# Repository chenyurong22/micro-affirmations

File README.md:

# µAffirmations
A microcontroller-based affection-giving MACHINE!

> [!IMPORTANT]
> This project is currently a work-in-progress, there __will__ be things that don't work, please bear with me will I work out the kinks!

# Table of Contents
- [Usage Guide](#usage-guide)
  - [Hardware](#hardware)
  - [Firmware](#firmware)
- [Project Updates](#project-updates)
- [Copyright and Licensing](#copyright-and-licensing)
- [Contact](#contact)

# Usage Guide
## Hardware
The PCB files can be found [here](/hw/pcb/RevB.zip), be sure of order a solder stencil too(ideally with a stencil unless you love hand-soldering 200+ SMD connections). The [BOM](/hw/pcb/micro-affirmations_BOM.csv) will provide you with a list of parts required. Due to the limited size on the PCB, many of the reference designators have been removed to save space. Because of this, you will likely need to have KiCAD running as you are placing components.

## Firmware
You will need access to an ST-Link programming device and have Platform IO installed via VS code. Once you're ready, upload the code by:
- Cloning the repository
- Open in VS code
- Connect the ST-Link programmer to your computer
- Connect the µAffirmations' programming port to the ST-Link programmer
- Ensure the µAffirmations board is powered
- Open the STM32 for VS Code extention
- Click __Upload__

<!--
### Message customisation
This device allows the user to create their own custom messages to be displayed on the LED matrix, to provide your messages, modify the following code found in [this](/path/to/file.c) file.

For axample:
```c
uint8_t someVar = 0;
```
-->

# Project Updates
## Hardware [RevB](https://github.com/i-Saac-IV/micro-affirmations/tree/v0.9.1)
After hardware tesing the following fixes have been made to the hardware design:
- Supercapcitor charging circuit, now uses a dedecated IC
- LED matrix layout, the LED spacing has been decreased
- LED brightness was assessed and appropriate resistor have been selected
- The overall PCB dimentions have shrunk to 70x40mm

## Hardware [RevA](https://github.com/i-Saac-IV/micro-affirmations/tree/v0.9.0)
Initial hardware design.

# Copyright and Licensing
See [licence](LICENSE) for in depth info.
<!--
This project uses the following third-party libraries:

- Lib ( License)

Copyright and license terms belong to their respective authors.

Contact me if anything here is incorrect.
-->

# Contact
If you'd like to get in touch, feel free to reach out!
<p>

</p>

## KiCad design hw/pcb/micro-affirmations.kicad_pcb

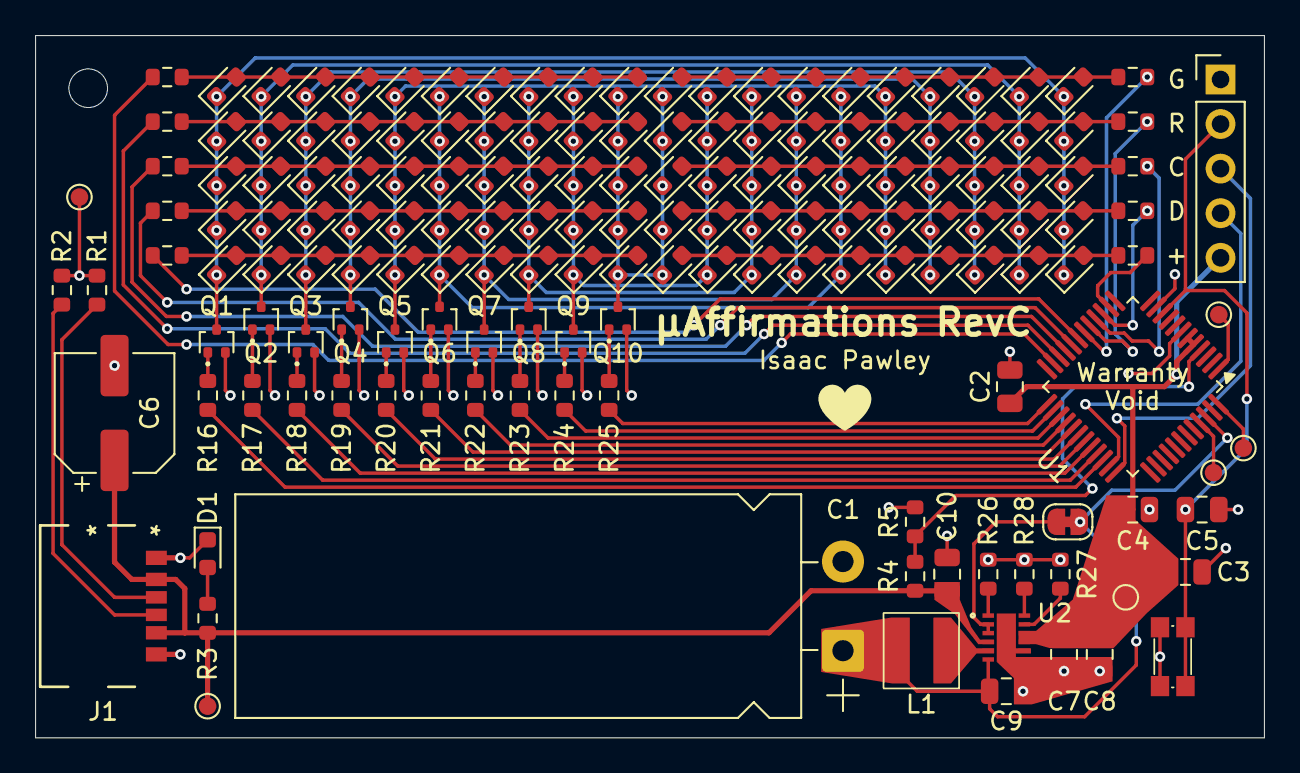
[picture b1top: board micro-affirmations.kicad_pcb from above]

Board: 2 copper layers, 70.0 x 40.0 mm, 164 parts (1 on the bottom side), 70 nets.

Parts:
C1: 15F; CP_Radial_L32.0mm_D12.5mm_P5.00mm_Horizontal
C2: 4.7u; C_0805_2012Metric
C3, C4, C5: 100n; C_0805_2012Metric
C6: 100u; CP_Elec_6.3x5.4_Nichicon
C7, C8, C9, C10: 10u; C_0805_2012Metric
D1: CHARGE; D_0603_1608Metric
D5, D6, D7, D8, D9, D10, D11, D12, D13, D14, D15, D16, D17, D18, D19, D20, D21, D22, D23, D24, D25, D26, D27, D28, D29, D30, D31, D32, D33, D34, D35, D36, D37, D38, D39, D40, D41, D42, D43, D44, D45, D46, D47, D48, D49, D50, D51, D52, D53, D54, D55, D56, D57, D58, D59, D60, D61, D62, D63, D64, D65, D66, D67, D68, D69, D70, D71, D72, D73, D74, D75, D76, D77, D78, D79, D80, D81, D82, D83, D84, D85, D86, D87, D88, D89, D90, D91, D92, D93, D94, D95, D96, D97, D98, D99, D100, D101, D102, D103, D104: LED; D_0603_1608Metric
H1: MountingHole; MountingHole_2.2mm_M2
J1: USBC; 2171750001_MOL
J2: DEBUG; PinHeader_1x05_P2.54mm_Vertical
JP1: SolderJumper_2_Bridged; SolderJumper-2_P1.3mm_Bridged_RoundedPad1.0x1.5mm
L1: 2.2u; L_1616_4040Metric
Q1, Q2, Q3, Q4, Q5, Q6, Q7, Q8, Q9, Q10: NCH; SOT-416
R1, R2, R4: 5.1k; R_0603_1608Metric
R3: 1.5k; R_0603_1608Metric
R5: 10k; R_0603_1608Metric
R6, R7, R8, R9, R10, R11, R12, R13, R14, R15: 820; R_0603_1608Metric
R16, R17, R18, R19, R20, R21, R22, R23, R24, R25: 100; R_0603_1608Metric
R26: 4.75k; R_0603_1608Metric
R27: 75.0k; R_0603_1608Metric
R28: 13.0k; R_0603_1608Metric
SW1: RST; TL1030_A
TP2, TP3, TP4, TP5, TP6, TP7, TP8: TestPoint; TestPoint_Pad_D1.0mm
U1: STM32C031C6Tx; LQFP-48_7x7mm_P0.5mm
U2: TPS61094; WSON_94DSSR_TEX

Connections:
+3V3: C2.1, C3.1, C4.1, C7.1, C8.1, J2.5, TP3.1 (1_1), U1.5 (VREF+), U1.6 (VDD), U2.9 (VOUT), U2.10 (VOUT)
+5V: C6.1, C10.1, J1.A9 (VBUS), J1.B9 (VBUS), R3.1, R4.2, TP2.1 (1_1), U2.4 (VIN)
/CHARGE_SENSE: R4.1, R5.2, U1.4 (PF3)
/DEBUG_SWCLK: J2.3, U1.36 (PA14)
/DEBUG_SWDIO: J2.4, U1.35 (PA13)
/MATRIX_A0: R6.1, U1.23 (PB11)
/MATRIX_A1: R7.1, U1.22 (PB10)
/MATRIX_A2: R8.1, U1.21 (PB2)
/MATRIX_A3: R9.1, U1.20 (PB1)
/MATRIX_A4: R10.1, U1.19 (PB0)
/MATRIX_A5: R11.1, U1.18 (PA7)
/MATRIX_A6: R12.1, U1.17 (PA6)
/MATRIX_A7: R13.1, U1.16 (PA5)
/MATRIX_A8: R14.1, U1.15 (PA4)
/MATRIX_A9: R15.1, U1.14 (PA3)
/MATRIX_K0: R16.1, U1.34 (PA12)
/MATRIX_K1: R17.1, U1.33 (PA11)
/MATRIX_K2: R18.1, U1.32 (PA10)
/MATRIX_K3: R19.1, U1.31 (PC7)
/MATRIX_K4: R20.1, U1.30 (PC6)
/MATRIX_K5: R21.1, U1.29 (PA9)
/MATRIX_K6: R22.1, U1.28 (PA8)
/MATRIX_K7: R23.1, U1.27 (PB15)
/MATRIX_K8: R24.1, U1.26 (PB14)
/MATRIX_K9: R25.1, U1.25 (PB13)
/NRST: C5.1, J2.2, SW1.2, U1.10 (PF2)
CAP_VOLT: C1.1, C9.1, JP1.1 (A), L1.2, U1.46 (PB7), U2.6 (SUP)
GND: C1.2, C2.2, C3.2, C4.2, C5.2, C6.2, C7.2, C8.2, C9.2, C10.2, D1.1 (K), J1.A12 (GND), J1.B12 (GND), J2.1, Q1.2 (S), Q2.2 (S), Q3.2 (S), Q4.2 (S), Q5.2 (S), Q6.2 (S), Q7.2 (S), Q8.2 (S), Q9.2 (S), Q10.2 (S), R1.2, R2.2, R5.1, R26.1, R27.1, R28.1, SW1.1, TP8.1 (1_1), U1.7 (VSS), U2.7 (PGND), U2.8 (AGND), U2.13
unnamed: D1.2 (A), R3.2
unnamed: D5.2 (A), D6.2 (A), D7.2 (A), D8.2 (A), D9.2 (A), D10.2 (A), D11.2 (A), D12.2 (A), D13.2 (A), D14.2 (A), R6.2
unnamed: D10.1 (K), D20.1 (K), D30.1 (K), D40.1 (K), D50.1 (K), D60.1 (K), D70.1 (K), D80.1 (K), D90.1 (K), D100.1 (K), Q6.3 (D)
unnamed: D15.2 (A), D16.2 (A), D17.2 (A), D18.2 (A), D19.2 (A), D20.2 (A), D21.2 (A), D22.2 (A), D23.2 (A), D24.2 (A), R7.2
unnamed: D5.1 (K), D15.1 (K), D25.1 (K), D35.1 (K), D45.1 (K), D55.1 (K), D65.1 (K), D75.1 (K), D85.1 (K), D95.1 (K), Q1.3 (D)
unnamed: D6.1 (K), D16.1 (K), D26.1 (K), D36.1 (K), D46.1 (K), D56.1 (K), D66.1 (K), D76.1 (K), D86.1 (K), D96.1 (K), Q2.3 (D)
unnamed: D7.1 (K), D17.1 (K), D27.1 (K), D37.1 (K), D47.1 (K), D57.1 (K), D67.1 (K), D77.1 (K), D87.1 (K), D97.1 (K), Q3.3 (D)
unnamed: D8.1 (K), D18.1 (K), D28.1 (K), D38.1 (K), D48.1 (K), D58.1 (K), D68.1 (K), D78.1 (K), D88.1 (K), D98.1 (K), Q4.3 (D)
unnamed: D9.1 (K), D19.1 (K), D29.1 (K), D39.1 (K), D49.1 (K), D59.1 (K), D69.1 (K), D79.1 (K), D89.1 (K), D99.1 (K), Q5.3 (D)
unnamed: D25.2 (A), D26.2 (A), D27.2 (A), D28.2 (A), D29.2 (A), D30.2 (A), D31.2 (A), D32.2 (A), D33.2 (A), D34.2 (A), R8.2
unnamed: D35.2 (A), D36.2 (A), D37.2 (A), D38.2 (A), D39.2 (A), D40.2 (A), D41.2 (A), D42.2 (A), D43.2 (A), D44.2 (A), R9.2
unnamed: D45.2 (A), D46.2 (A), D47.2 (A), D48.2 (A), D49.2 (A), D50.2 (A), D51.2 (A), D52.2 (A), D53.2 (A), D54.2 (A), R10.2
unnamed: D55.2 (A), D56.2 (A), D57.2 (A), D58.2 (A), D59.2 (A), D60.2 (A), D61.2 (A), D62.2 (A), D63.2 (A), D64.2 (A), R11.2
unnamed: D65.2 (A), D66.2 (A), D67.2 (A), D68.2 (A), D69.2 (A), D70.2 (A), D71.2 (A), D72.2 (A), D73.2 (A), D74.2 (A), R12.2
unnamed: D75.2 (A), D76.2 (A), D77.2 (A), D78.2 (A), D79.2 (A), D80.2 (A), D81.2 (A), D82.2 (A), D83.2 (A), D84.2 (A), R13.2
unnamed: D85.2 (A), D86.2 (A), D87.2 (A), D88.2 (A), D89.2 (A), D90.2 (A), D91.2 (A), D92.2 (A), D93.2 (A), D94.2 (A), R14.2
unnamed: D95.2 (A), D96.2 (A), D97.2 (A), D98.2 (A), D99.2 (A), D100.2 (A), D101.2 (A), D102.2 (A), D103.2 (A), D104.2 (A), R15.2
unnamed: D11.1 (K), D21.1 (K), D31.1 (K), D41.1 (K), D51.1 (K), D61.1 (K), D71.1 (K), D81.1 (K), D91.1 (K), D101.1 (K), Q7.3 (D)
unnamed: D12.1 (K), D22.1 (K), D32.1 (K), D42.1 (K), D52.1 (K), D62.1 (K), D72.1 (K), D82.1 (K), D92.1 (K), D102.1 (K), Q8.3 (D)
unnamed: D13.1 (K), D23.1 (K), D33.1 (K), D43.1 (K), D53.1 (K), D63.1 (K), D73.1 (K), D83.1 (K), D93.1 (K), D103.1 (K), Q9.3 (D)
unnamed: D14.1 (K), D24.1 (K), D34.1 (K), D44.1 (K), D54.1 (K), D64.1 (K), D74.1 (K), D84.1 (K), D94.1 (K), D104.1 (K), Q10.3 (D)
unnamed: J1.A5 (CC1), R1.1
unnamed: J1.B5 (CC2), R2.1
unnamed: JP1.2 (B), U2.2 (MODE), U2.3 (EN)
unnamed: Q1.1 (G), R16.2
unnamed: Q2.1 (G), R17.2
unnamed: Q3.1 (G), R18.2
unnamed: Q4.1 (G), R19.2
unnamed: Q5.1 (G), R20.2
unnamed: Q6.1 (G), R21.2
unnamed: Q7.1 (G), R22.2
unnamed: Q8.1 (G), R23.2
unnamed: Q9.1 (G), R24.2
unnamed: Q10.1 (G), R25.2
unnamed: TP7.1 (1_1), U1.11 (PA0)
unnamed: TP5.1 (1_1), U1.45 (PB6)
unnamed: TP4.1 (1_1), U1.48 (PB9)
unnamed: TP6.1 (1_1), U1.1 (PC13)
unnamed: R27.2, U2.11 (ICHG)
unnamed: R26.2, U2.1 (OSEL)
unnamed: L1.1, U2.5 (SW)
unnamed: R28.2, U2.12 (VCHG)

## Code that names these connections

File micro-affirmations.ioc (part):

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Mcu.Name=STM32C031C(4-6)Tx
Mcu.Package=LQFP48
Mcu.UserName=STM32C031C6Tx
PA1.GPIOParameters=GPIO_Label
PA1.GPIO_Label=RANDOM
PA1.Mode=IN1
PA1.Signal=ADC1_IN1
PA10.GPIOParameters=GPIO_Label
PA10.GPIO_Label=MATRIX_K2
PA10.Signal=GPIO_Output
PA11\ [PA9].GPIOParameters=GPIO_Label
PA11\ [PA9].GPIO_Label=MATRIX_K1
PA11\ [PA9].Signal=GPIO_Output
PA12\ [PA10].GPIOParameters=GPIO_Label
PA12\ [PA10].GPIO_Label=MATRIX_K0
PA12\ [PA10].Signal=GPIO_Output
PA13.Mode=Serial_Wire
PA13.Signal=DEBUG_SWDIO
PA14-BOOT0.Mode=Serial_Wire
PA14-BOOT0.Signal=DEBUG_SWCLK
PA3.GPIOParameters=GPIO_Label
PA3.GPIO_Label=MATRIX_A9
PA3.Signal=GPIO_Output
PA4.GPIOParameters=GPIO_Label
PA4.GPIO_Label=MATRIX_A8
PA4.Signal=GPIO_Output
PA5.GPIOParameters=GPIO_Label
PA5.GPIO_Label=MATRIX_A7
PA5.Signal=GPIO_Output
PA6.GPIOParameters=GPIO_Label
PA6.GPIO_Label=MATRIX_A6
PA6.Signal=GPIO_Output
PA7.GPIOParameters=GPIO_Label
PA7.GPIO_Label=MATRIX_A5
PA7.Signal=GPIO_Output
PA8.GPIOParameters=GPIO_Label
PA8.GPIO_Label=MATRIX_K6
PA8.Signal=GPIO_Output
PA9.GPIOParameters=GPIO_Label
PA9.GPIO_Label=MATRIX_K5
PA9.Signal=GPIO_Output
PB0.GPIOParameters=GPIO_Label
PB0.GPIO_Label=MATRIX_A4
PB0.Signal=GPIO_Output
PB1.GPIOParameters=GPIO_Label
PB1.GPIO_Label=MATRIX_A3
PB1.Signal=GPIO_Output
PB10.GPIOParameters=GPIO_Label
PB10.GPIO_Label=MATRIX_A1
PB10.Signal=GPIO_Output
PB11.GPIOParameters=GPIO_Label
PB11.GPIO_Label=MATRIX_A0
PB11.Signal=GPIO_Output
PB13.GPIOParameters=GPIO_Label
PB13.GPIO_Label=MATRIX_K9
PB13.Signal=GPIO_Output
PB14.GPIOParameters=GPIO_Label
PB14.GPIO_Label=MATRIX_K8
PB14.Signal=GPIO_Output
PB15.GPIOParameters=GPIO_Label
PB15.GPIO_Label=MATRIX_K7
PB15.Signal=GPIO_Output
PB2.GPIOParameters=GPIO_Label
PB2.GPIO_Label=MATRIX_A2
PB2.Signal=GPIO_Output
PB7.GPIOParameters=GPIO_Label
PB7.GPIO_Label=CAP_VOLT
PB7.Signal=GPIO_Analog
PC6.GPIOParameters=GPIO_Label
PC6.GPIO_Label=MATRIX_K4
PC6.Signal=GPIO_Output
PC7.GPIOParameters=GPIO_Label
PC7.GPIO_Label=MATRIX_K3
PC7.Signal=GPIO_Output
PF3.GPIOParameters=GPIO_Label
PF3.GPIO_Label=CHARGE_SENSE
PF3.Signal=GPIO_Input
RCC.HSE_VALUE=8000000
RCC.SYSCLKFreq_VALUE=48000000
board=custom

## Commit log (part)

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2026-05-11 chore: added charger footprints
2026-05-11 chore: updated project data
2026-05-11 chore: updated schematic to have correctly sized current limiting resistors
2026-05-11 chore: redesigned pcb, new capacitor charger and smaller matrix
2026-05-11 chore: updated schematics to show true part numbers
2026-05-15 docs: updated readme
